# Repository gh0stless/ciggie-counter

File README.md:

# Ciggie Counter & Butt Bin

Count your cigarettes, see your patterns, pace yourself, without ads, accounts or tracking.

*Butt Bin design renders: the counting knob slips over the plunger grip of a spin ashtray (not built yet).*

This repository contains three parts that work on their own or together:

| Part | Folder | What it does |
|---|---|---|
| **Ciggie Counter** (Android app) | [`android-counter/`](android-counter/) | Counter with +1 button, history, statistics, break timer, reminders, optional calendar summary and Nextcloud sync. English and German. |
| **Butt Bin** (hardware, prototype) | [`firmware/`](firmware/) | An ashtray with a plunger that counts every cigarette you stub out, stores it with a timestamp and hands it to the app via Bluetooth LE, even when the phone was away. |
| **Nextcloud app** `cigarettecounter` | [`nextcloud-app/cigarettecounter/`](nextcloud-app/cigarettecounter/) | Self-hosted web app/PWA with the same counting logic; lets several devices (phone, tablet) share one state. |
| **Home Assistant integration** `ciggie_counter` | [gh0stless/ciggie-counter-ha](https://github.com/gh0stless/ciggie-counter-ha) | Standalone counting in Home Assistant (HACS): sensors, reminders as events, count with any button or contact; the Android app can sync with it like with Nextcloud. |

More about the Butt Bin: <https://crazy-midi.de>

## Ciggie Counter (Android)

- Android 13 or newer, no Google Play Services needed (runs fine on GrapheneOS).
- All data stays on the device. Optional: your own Nextcloud with the `cigarettecounter` app, which can also send voice announcements to Home Assistant.
- Permissions are only used when the matching feature is switched on: notifications (reminders), exact alarms (punctual reminders), calendar (daily summary), Bluetooth scan/connect without location (Butt Bin), internet (Nextcloud).

### Build

```sh
cd android-counter
./gradlew assembleDebug        # app/build/outputs/apk/debug/app-debug.apk
./gradlew assembleRelease      # signed only if android-counter/keystore.properties exists
```

Requires JDK 17+ (e.g. the one bundled with Android Studio) and the Android SDK.

### Translations

All texts are in `android-counter/app/src/main/res/values/strings.xml` (English) and `values-de/strings.xml` (German). A new language only needs a translated copy in `values-<code>/`.

> **A small piece of unsolicited advice 🤓:** your phone does not belong in your home network. It runs dozens of apps you cannot look into, so put it in the **guest Wi-Fi** and keep your servers, NAS and smart home in the main network. Ciggie Counter is built for that: the phone talks to Home Assistant or Nextcloud over **HTTPS** like any other device on the internet – no open ports towards the phone, no local network access needed.

> **Keep the clocks in sync ⏱️:** with several systems (phone, Nextcloud, Home Assistant, watch) every entry carries the time of the device that counted it. Reminders ("you may smoke again", "did you count them all?") and announcements are computed from those times, and Home Assistant only announces entries younger than 10 minutes. A server clock that is a few minutes off is enough for announcements to go missing or reminders to come early. Check that every server really synchronises its time (on Home Assistant OS: `timedatectl status` in the host shell must say `System clock synchronized: yes`).

## Butt Bin (firmware)

Prototype on a Telink TLSR825x (dev board TLSR8258DK48, target module Ebyte E104-BT12LSP with TLSR8253).

- Counts plunger presses, stores them with time in a flash ring buffer, works without a phone nearby.
- Advertises the current count; the app wakes up via a background Bluetooth scan and fetches new events within seconds.
- Low-power: deep sleep with RAM retention between events.

Building needs the [Telink TC BLE SDK](https://github.com/telink-semi/tc_ble_sdk) (V4.0.2.5) in `firmware/tc_ble_sdk/` and the TC32 toolchain, see `firmware/build_b85.sh` and `firmware/flash_b85.sh`. Short German notes on the chips and tools are in [`datasheets/`](datasheets/).

The firmware is derived from the SDK example `acl_peripheral_demo`; files taken from the SDK keep their Apache-2.0 headers.

A first schematic draft for the board (Ai-Thinker TB-03F module powered directly from a CR2450 coin cell, roughly 2–4 years per cell, button input, six LEDs on three dimmable channels for a running light in the knob's light ring, and labelled through-hole pads for I2C, a second button, a pump output, an optional fourth LED channel and two spare pins) is in [`hardware/kicad/buttbin_carrier/`](hardware/kicad/buttbin_carrier/) with a first generated two-layer layout, 34 mm round with two flats for pogo-pin clips (programming row and expansion row) (KiCad 10, not yet built or tested).

The knob is modelled in FreeCAD in [`hardware/freecad/`](hardware/freecad/): it slips over the plunger grip of the "Value" spin ashtray (rubber sleeve), is 40 mm wide and about 80 mm high, and holds the cell, the board and a clear light ring; on top sits a low-profile mechanical arcade button (Retro+ S30). Hood and base are meant to be 3D-printed. Renders are in [`design/fotoshooting/`](design/fotoshooting/).

## Nextcloud app

Install by copying `nextcloud-app/cigarettecounter/` to your Nextcloud `apps/` (or `custom_apps/`) folder, run `composer install --no-dev` inside it and enable the app. The Android app talks to it with an app password (Settings → Security). For Home Assistant use the integration [gh0stless/ciggie-counter-ha](https://github.com/gh0stless/ciggie-counter-ha): it syncs with this app and does the announcements (TTS, Telegram) and voice commands.

## License

- Project: [GNU GPL v3](LICENSE)
- Nextcloud app: [GNU AGPL v3](nextcloud-app/cigarettecounter/LICENSE)
- Files from the Telink SDK: Apache-2.0 (see file headers)

This is a hobby project. It is not a medical product and does not give health advice.

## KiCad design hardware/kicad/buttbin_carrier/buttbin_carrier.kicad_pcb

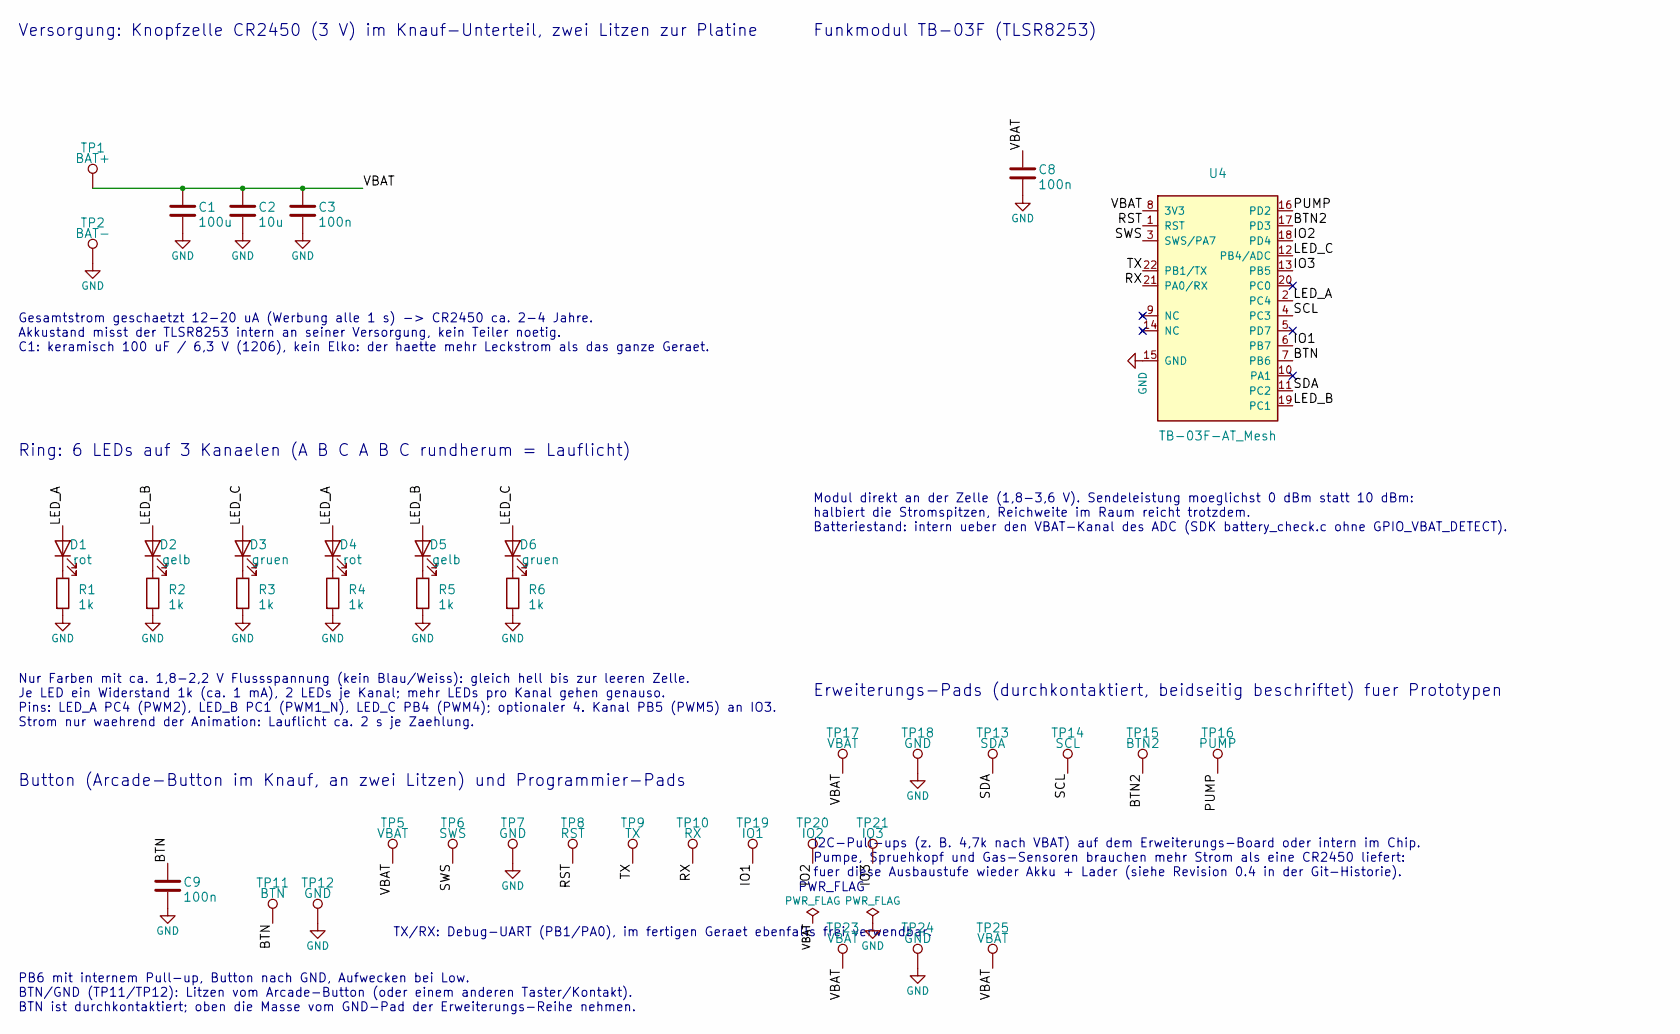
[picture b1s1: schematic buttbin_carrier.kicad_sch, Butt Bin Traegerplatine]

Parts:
C1: 100u; C_1206_3216Metric; LCSC C15008
C2: 10u; C_0603_1608Metric; LCSC C19702
C3, C8, C9: 100n; C_0603_1608Metric; LCSC C14663
D1, D4: rot; LED_0603_1608Metric; LCSC C2286
D2, D5: gelb; LED_0603_1608Metric; LCSC C7429912
D3, D6: gruen; LED_0603_1608Metric; LCSC C7429914
R1, R2, R3, R4, R5, R6: 1k; R_0603_1608Metric; LCSC C21190
TP1: BAT+; TestPoint_THTPad_1.5x1.5mm_Drill0.7mm
TP2: BAT-; TestPoint_THTPad_1.5x1.5mm_Drill0.7mm
TP5: VBAT; TestPoint_Pad_D1.5mm
TP6: SWS; TestPoint_Pad_D1.5mm
TP7: GND; TestPoint_Pad_D1.5mm
TP8: RST; TestPoint_Pad_D1.5mm
TP9: TX; TestPoint_THTPad_D1.5mm_Drill0.7mm
TP10: RX; TestPoint_THTPad_D1.5mm_Drill0.7mm
TP11: BTN; TestPoint_THTPad_1.5x1.5mm_Drill0.7mm
TP12: GND; TestPoint_Pad_1.5x1.5mm
TP13: SDA; TestPoint_THTPad_D1.5mm_Drill0.7mm
TP14: SCL; TestPoint_THTPad_D1.5mm_Drill0.7mm
TP15: BTN2; TestPoint_THTPad_D1.5mm_Drill0.7mm
TP16: PUMP; TestPoint_THTPad_D1.5mm_Drill0.7mm
TP17, TP23, TP25: VBAT; TestPoint_THTPad_D1.5mm_Drill0.7mm
TP18, TP24: GND; TestPoint_THTPad_D1.5mm_Drill0.7mm
TP19: IO1; TestPoint_THTPad_D1.5mm_Drill0.7mm
TP20: IO2; TestPoint_THTPad_D1.5mm_Drill0.7mm
TP21: IO3; TestPoint_THTPad_D1.5mm_Drill0.7mm
U4: TB-03F-AT_Mesh; ESP-12E; LCSC C2764070

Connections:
/BTN: C9.1, TP11.1, U4.7 (PB6)
/BTN2: TP15.1, U4.17 (PD3)
/IO1: TP19.1, U4.6 (PB7)
/IO2: TP20.1, U4.18 (PD4)
/IO3: TP21.1, U4.13 (PB5)
/LED_A: D1.2 (A), D4.2 (A), U4.2 (PC4)
/LED_B: D2.2 (A), D5.2 (A), U4.19 (PC1)
/LED_C: D3.2 (A), D6.2 (A), U4.12 (PB4/ADC)
/PUMP: TP16.1, U4.16 (PD2)
/RST: TP8.1, U4.1 (RST)
/RX: TP10.1, U4.21 (PA0/RX)
/SCL: TP14.1, U4.4 (PC3)
/SDA: TP13.1, U4.11 (PC2)
/SWS: TP6.1, U4.3 (SWS/PA7)
/TX: TP9.1, U4.22 (PB1/TX)
/VBAT: C1.1, C2.1, C3.1, C8.1, TP1.1, TP5.1, TP17.1, TP23.1, TP25.1, U4.8 (3V3)
GND: C1.2, C2.2, C3.2, C8.2, C9.2, R1.2, R2.2, R3.2, R4.2, R5.2, R6.2, TP2.1, TP7.1, TP12.1, TP18.1, TP24.1, U4.15 (GND)
unnamed: D1.1 (K), R1.1
unnamed: D2.1 (K), R2.1
unnamed: D3.1 (K), R3.1
unnamed: D4.1 (K), R4.1
unnamed: D5.1 (K), R5.1
unnamed: D6.1 (K), R6.1

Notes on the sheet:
Versorgung: Knopfzelle CR2450 (3 V) im Knauf-Unterteil, zwei Litzen zur Platine
Gesamtstrom geschaetzt 12-20 uA (Werbung alle 1 s) -> CR2450 ca. 2-4 Jahre. Akkustand misst der TLSR8253 intern an seiner Versorgung, kein Teiler noetig. C1: keramisch 100 uF / 6,3 V (1206), kein Elko: der haette mehr Leckstrom als das ganze Geraet.
Ring: 6 LEDs auf 3 Kanaelen (A B C A B C rundherum = Lauflicht)
Nur Farben mit ca. 1,8-2,2 V Flussspannung (kein Blau/Weiss): gleich hell bis zur leeren Zelle. Je LED ein Widerstand 1k (ca. 1 mA), 2 LEDs je Kanal; mehr LEDs pro Kanal gehen genauso. Pins: LED_A PC4 (PWM2), LED_B PC1 (PWM1_N), LED_C PB4 (PWM4); optionaler 4. Kanal PB5 (PWM5) an IO3. Strom nur wae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
Funkmodul TB-03F (TLSR8253)
Modul direkt an der Zelle (1,8-3,6 V). Sendeleistung moeglichst 0 dBm statt 10 dBm: halbiert die Stromspitzen, Reichweite im Raum reicht trotzdem. Batteriestand: intern ueber den VBAT-Kanal des ADC (SDK battery_check.c ohne GPIO_VBAT_DETECT).
Erweiterungs-Pads (durchkontaktiert, beidseitig beschriftet) fuer Prototypen
I2C-Pull-ups (z. B. 4,7k nach VBAT) auf dem Erweiterungs-Board oder intern im Chip. Pumpe, Spruehkopf und Gas-Sensoren brauchen mehr Strom als eine CR2450 liefert: fuer diese Ausbaustufe wieder Akku + Lader (siehe Revision 0.4 in der Git-Historie).
Button (Arcade-Button im Knauf, an zwei Litzen) und Programmier-Pads
PB6 mit internem Pull-up, Button nach GND, Aufwecken bei Low. BTN/GND (TP11/TP12): Litzen vom Arcade-Button (oder einem anderen Taster/Kontakt). BTN ist durchkontaktiert; oben die Masse vom GND-Pad der Erweiterungs-Reihe nehmen.
TX/RX: Debug-UART (PB1/PA0), im fertigen Geraet ebenfalls frei verwendbar.
PWR_FLAG

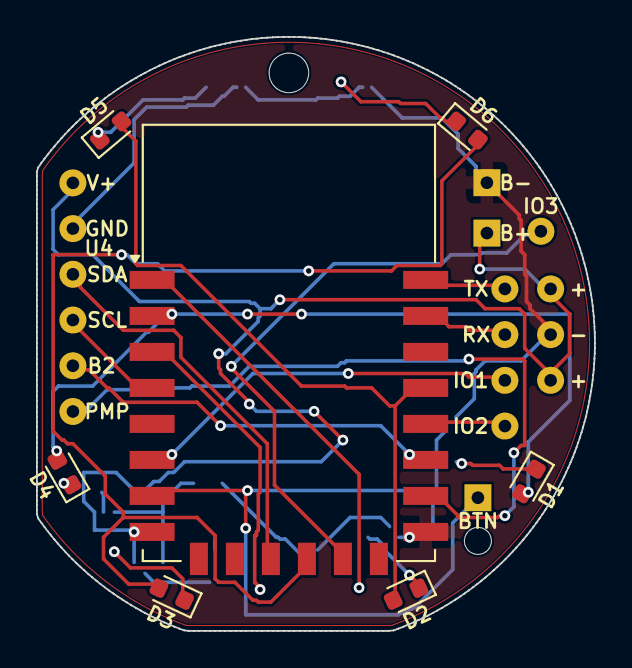
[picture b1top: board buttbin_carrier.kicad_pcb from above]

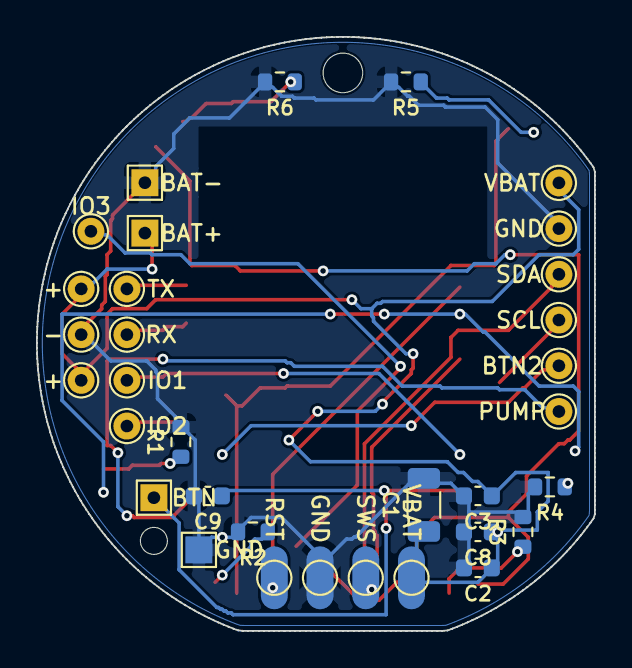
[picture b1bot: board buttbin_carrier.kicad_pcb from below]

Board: 2 copper layers, 31.0 x 33.0 mm, 42 parts (33 on the bottom side), 23 nets.

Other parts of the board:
H1: Nase
H2: M2

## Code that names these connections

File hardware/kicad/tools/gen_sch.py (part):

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                 bottom=[("2", "GND", PI)],
                 width=15.24, desc="LDO 3,3 V, 200 nA Ruhestrom, EN mit internem Pulldown")
TB03 = box_symbol("ButtBin:TB-03F", "U", "TB-03F (TLSR8253)", "RF_Module:ESP-12E",
                  left=[("8", "3V3", PI), ("1", "RST", "input"), ("3", "SWS/PA7", B), None,
                        ("22", "PB1/TX", B), ("21", "PA0/RX", B), None, ("9", "NC", NC), ("14", "NC", NC),
                        None, ("15", "GND", PI)],
                  right=[("16", "PD2", B), ("17", "PD3", B), ("18", "PD4", B), ("12", "PB4/ADC", B),
                         ("13", "PB5", B), ("20", "PC0", B), ("2", "PC4", B), ("4", "PC3", B),
                         ("5", "PD7", B), ("6", "PB7", B), ("7", "PB6", B), ("10", "PA1", B),
                         ("11", "PC2", B), ("19", "PC1", B)],
                  width=20.32, desc="Ai-Thinker TB-03F-AT_Mesh, TLSR8253, Pads wie ESP-12")

SYMS = [R, C, LED, TP, GND, FLAG, TB03]
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text("Ring: 6 LEDs auf 3 Kanaelen (A B C A B C rundherum = Lauflicht)", 17.78, 96.52, TITLE)
# 3 Kanaele, jeder mit eigenem PWM-Kanal (dimmbar). Im Ring reihum angeschlossen:
# schaltet die Firmware A, B, C nacheinander, laeuft das Licht rundherum.
# 6 statt 8 LEDs, damit der Ring spiegelsymmetrisch bleibt; der 4. Kanal (PB5) geht als Pad IO3 heraus.
# Everlight 19-213 (AlGaInP, max. 2,3-2,4 V): auch Gruen (565 nm) leuchtet noch an der fast leeren Zelle;
# Smaragdgruen (520 nm, InGaN) braucht ~3 V und bleibt an der CR2450 dunkel
CHANNELS = [("LED_A", "rot", "", "2"),     # 19-213/R6C-AQ1R2B, PC4, PWM2
            ("LED_B", "gelb", "", "19"),   # 19-213/Y2C-CQ2R2L/3T, PC1, PWM1_N (PWM1 frei, PC3 ist I2C)
            ("LED_C", "gruen", "", "12")]  # 19-213/G6C-AP1Q2/3T, PB4, PWM4
N_LED = 6
# je LED ein Vorwiderstand (0603, von Hand loetbar) unten direkt unter der LED: die Kathoden-Netze bleiben
# kurz (ein gemeinsamer Widerstand je Kanal braeuchte Leitungen quer ueber die Platine, um die Antenne herum)
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    res("R%d" % (i + 1), "330", "C23138", x, 119.38, {"1": "W", "2": "GND"})
text("Nur Farben mit ca. 1,8-2,2 V Flussspannung (kein Blau/Weiss): gleich hell bis zur leeren Zelle.\n"
     "Je LED ein Widerstand 330R (ca. 2,5-3 mA), 2 LEDs je Kanal; dunkler per PWM. Nie alle 6 voll zugleich (~18 mA).\n"
     "Pins: LED_A PC4 (PWM2), LED_B PC1 (PWM1_N), LED_C PB4 (PWM4); optionaler 4. Kanal PB5 (PWM5) an IO3.\n"
     "Strom nur waehrend der Animation: Lauflicht ca. 2 s je Zaehlung.", 17.78, 142.24, FONT)

# ============ Modul ============
text("Funkmodul TB-03F (TLSR8253)", 152.4, 25.4, TITLE)
place(TB03, "U4", "TB-03F-AT_Mesh", 220.98, 71.12,
      dict({"8": "VBAT", "1": "RST", "3": "SWS", "22": "TX", "21": "RX", "9": "NC", "14": "NC", "15": "GND",
            "7": "BTN",     # PB6: Button (PB5 bleibt fuer den optionalen PWM5-Kanal an IO3)
            # alle uebrigen GPIOs offen; Ring, Erweiterungen und Reserve ueberschreiben die Zeilen darunter
            **{p: "NC" for p in ("2", "4", "5", "6", "10", "11", "12", "13", "16", "17", "18", "19", "20")}},
           **{p: net for net, _, _, p in CHANNELS},
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# Reihe im Raster 2,54 mm: Stiftleiste oder Litzen fuer Erweiterungs-Prototypen
for i, (ref, name, net, note) in enumerate([("TP17", "VBAT", "VBAT", "Versorgung fuer Erweiterungen"),
                                            ("TP18", "GND", "GND", "Masse fuer Erweiterungen"),
                                            ("TP13", "SDA", "SDA", "PC2, I2C-Daten (Umweltsensor, Display)"),
                                            ("TP14", "SCL", "SCL", "PC3, I2C-Takt"),
                                            ("TP15", "BTN2", "BTN2", "PD3, 2. Taster nach GND, weckt aus dem Schlaf"),
                                            ("TP16", "PUMP", "PUMP", "PD2 (PWM3), Gate eines MOSFETs fuer Pumpe/Spruehkopf")]):
    pad(ref, name, 157.48 + i * 12.7, 149.86, net, TP_THR, note)
text("I2C-Pull-ups (z. B. 4,7k nach VBAT) auf dem Erweiterungs-Board oder intern im Chip.\n"
     "Pumpe, Spruehkopf und Gas-Sensoren brauchen mehr Strom als eine CR2450 liefert:\n"
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cap("C9", "100n", "C14663", 43.18, 168.91, {"1": "BTN", "2": "GND"})
pad("TP11", "BTN", 60.96, 175.26, "BTN", TP_TH, "Button-Litze (durchkontaktiert)")
pad("TP12", "GND", 68.58, 175.26, "GND", "TestPoint:TestPoint_Pad_1.5x1.5mm", "Button-Masse (unten)")
text("PB6 mit internem Pull-up, Button nach GND, Aufwecken bei Low.\n"
     "BTN/GND (TP11/TP12): Litzen vom Arcade-Button (oder einem anderen Taster/Kontakt).\n"
     "BTN ist durchkontaktiert; oben die Masse vom GND-Pad der Erweiterungs-Reihe nehmen.", 17.78, 190.5, FONT)
# VBAT/SWS/GND/RST: runde Pads in einer Reihe (2,54 mm) an der Abflachung -> Pogo-Pin-Klemme
# TX/RX/IO1/IO2: zweite Reihe (2,54 mm) - Debug-UART und zwei Reserve-Pins fuer Unvorhergesehenes
for i, (name, net) in enumerate([("VBAT", "VBAT"), ("SWS", "SWS"), ("GND", "GND"),
                                 ("RST", "RST"), ("TX", "TX"), ("RX", "RX")]):
    pad("TP%d" % (5 + i), name, 81.28 + i * 10.16, 165.1, net,
        "TestPoint:TestPoint_Pad_D1.5mm" if i < 4 else TP_THR)   # Programmier-Reihe bleibt SMD (Klemme)
pad("TP19", "IO1", 81.28 + 6 * 10.16, 165.1, "IO1", TP_THR, "Reserve: PB7, ADC-faehig")
pad("TP20", "IO2", 81.28 + 7 * 10.16, 165.1, "IO2", TP_THR, "Reserve: PD4, PWM-faehig (PWM2_N)")
pad("TP21", "IO3", 81.28 + 8 * 10.16, 165.1, "IO3", TP_THR, "optionaler 4. LED-Kanal: PB5 (PWM5), sonst frei")
# zusaetzliche Versorgungs-Pads fuer die Weiterverwendung in anderen Bastelprojekten
for i, (ref, name, net) in enumerate([("TP23", "VBAT", "VBAT"), ("TP24", "GND", "GND"),
                                      ("TP25", "VBAT", "VBAT")]):
    pad(ref, name, 157.48 + i * 12.7, 182.88, net, TP_THR, "zusaetzliche Versorgung")
text("TX/RX: Debug-UART (PB1/PA0), im fertigen Geraet ebenfalls frei verwendbar.", 81.28, 177.8, FONT)

# ============ Netz-Treiber fuer den ERC ============
text("PWR_FLAG", 149.86, 170.18, FONT)
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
